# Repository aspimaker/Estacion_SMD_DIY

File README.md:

# Estacion_SMD_DIY
Base de soldadura SMD. Actualmente en desarrollo. No lo construyas todavía.

Utilizando un Arduino Nano, incluye el hardware necesario para calentar y controlar la temperatura usando una NTC y un SSR.
Incluye una pantalla OLED de 0.96", un enconder para moverse por el menú, algunos led y pulsadores.

Está diseñada para utilizar una tira led RGB los estados: frio, calentando, temperatura alcanzada, enfriando...
Puede que lo cambie por una tira WS2812B para simpliicar el diseño y la construcción.

Se podrán crear curvas de temperatura..

Agradezco tu colaboración para ayudarme a con posibles mejoras, corrección de errores, etc...

Gracias y un saludo.

#DIY_SMD_Station
SMD soldering station. Currently under development. Do not build it yet.

Using an Arduino Nano, it includes the necessary hardware for heating and temperature control using an NTC thermistor and an SSR.
It includes a 0.96" OLED screen, an encoder for navigating the menu, some LEDs, and pushbuttons.

It is designed to use an RGB LED strip with the following states: cold, heating, temperature reached, cooling, etc. I may change it to a WS2812B strip to simplify the design and construction.

Temperature curves can be created.

I appreciate your collaboration in helping me with possible improvements, bug fixes, etc.

Thank you and best regards.

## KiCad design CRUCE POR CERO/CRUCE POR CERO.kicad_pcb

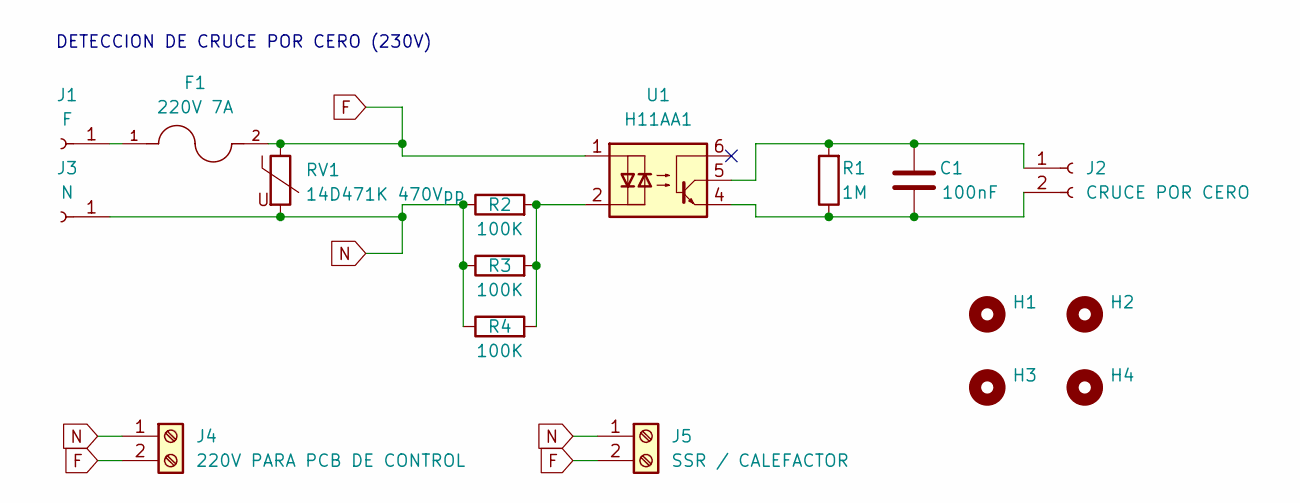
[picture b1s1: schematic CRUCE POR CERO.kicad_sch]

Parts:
C1: 100nF; C_Disc_D3.0mm_W2.0mm_P2.50mm
F1: 220V 7A; FUSIBLE BLX-A; PARTREV B
H1, H2, H3, H4: MountingHole; MountingHole_3.2mm_M3
J1: F; PinSocket_1x01_P2.54mm_Vertical
J2: CRUCE POR CERO; PinHeader_1x02_P2.54mm_Vertical
J3: N; PinSocket_1x01_P2.54mm_Vertical
J4: 220V PARA PCB DE CONTROL; TerminalBlock_Phoenix_MPT-0,5-2-2.54_1x02_P2.54mm_Horizontal
J5: SSR / CALEFACTOR; TerminalBlock_Phoenix_MPT-0,5-2-2.54_1x02_P2.54mm_Horizontal
R1: 1M; R_Axial_DIN0204_L3.6mm_D1.6mm_P5.08mm_Horizontal
R2, R3, R4: 100K; R_Axial_DIN0411_L9.9mm_D3.6mm_P5.08mm_Vertical
RV1: 14D471K 470Vpp; RV_Disc_D15.5mm_W7.5mm_P7.5mm
U1: H11AA1; DIP-6_W7.62mm

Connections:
F: F1.2, J4.2, J5.2, RV1.1, U1.1
N: J3.1, J4.1, J5.1, R2.1, R3.1, R4.1, RV1.2
unnamed: F1.1, J1.1
unnamed: C1.1, J2.1, R1.2, U1.5
unnamed: C1.2, J2.2, R1.1, U1.4
unnamed: R2.2, R3.2, R4.2, U1.2

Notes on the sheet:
DETECCION DE CRUCE POR CERO (230V)

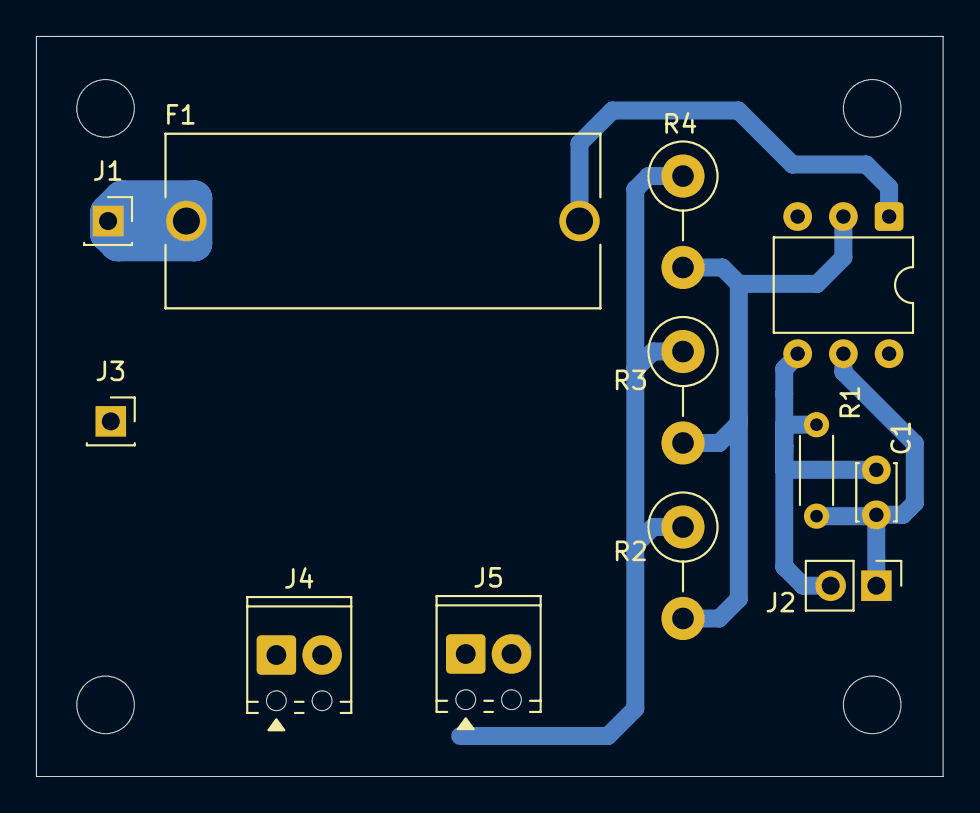
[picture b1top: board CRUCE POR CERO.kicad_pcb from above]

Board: 2 copper layers, 50.4 x 41.1 mm, 16 parts (0 on the bottom side), 6 nets.

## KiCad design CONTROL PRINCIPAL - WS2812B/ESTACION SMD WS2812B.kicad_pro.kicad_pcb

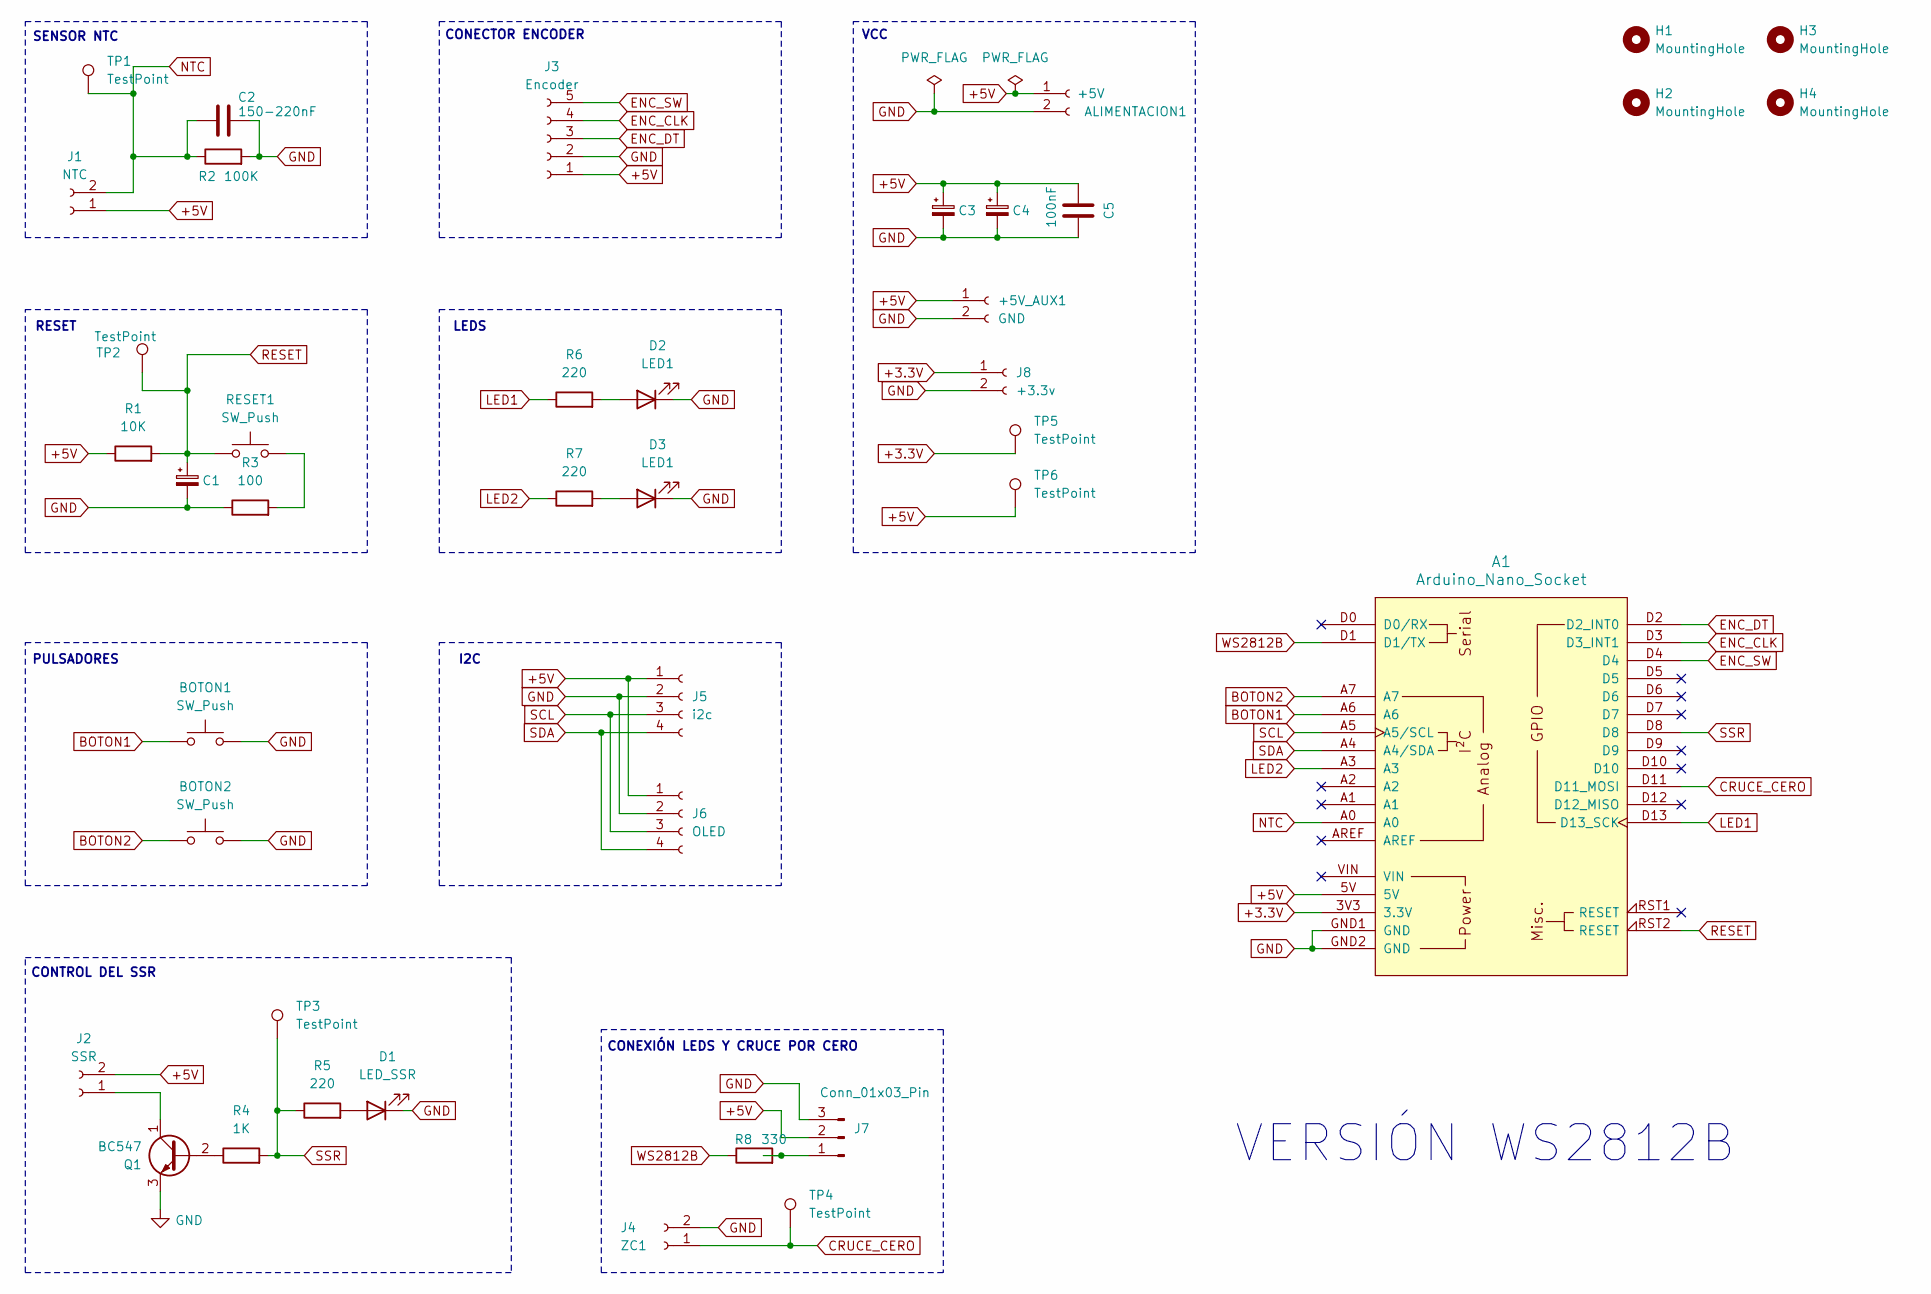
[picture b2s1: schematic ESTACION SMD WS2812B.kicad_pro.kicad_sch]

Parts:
+5V_AUX1: GND; PinHeader_1x02_P2.54mm_Vertical
A1: Arduino_Nano_Socket
ALIMENTACION1: +5V; PinHeader_1x02_P2.54mm_Vertical
BOTON1, BOTON2: SW_Push; PinHeader_1x02_P2.54mm_Vertical
C1, C4: 10uF/16V; CP_Radial_D5.0mm_P2.50mm
C2: 150-220nF; C_Disc_D3.0mm_W2.0mm_P2.50mm
C3: 1000uF/16V; CP_Radial_D10.0mm_P5.00mm
C5: 100nF; C_Disc_D3.0mm_W2.0mm_P2.50mm
D1: LED_SSR; LED_D3.0mm
D2, D3: LED1; LED_D3.0mm
H1, H2, H3, H4: MountingHole; MountingHole_3.2mm_M3
J1: NTC; PinHeader_1x02_P2.54mm_Vertical
J2: SSR; PinHeader_1x02_P2.54mm_Vertical
J3: Encoder; PinHeader_1x05_P2.54mm_Vertical
J4: ZC1; PinHeader_1x02_P2.54mm_Vertical
J5: i2c; PinHeader_1x04_P2.54mm_Vertical
J6: OLED; PinHeader_1x04_P2.54mm_Vertical
J7: Conn_01x03_Pin; PinHeader_1x03_P2.54mm_Vertical
J8: +3.3v; PinHeader_1x02_P2.54mm_Vertical
Q1: BC547; TO-92_Inline
R1: 10K; R_Axial_DIN0204_L3.6mm_D1.6mm_P5.08mm_Horizontal
R2: 100K; R_Axial_DIN0204_L3.6mm_D1.6mm_P5.08mm_Horizontal
R3: 100; R_Axial_DIN0204_L3.6mm_D1.6mm_P5.08mm_Horizontal
R4: 1K; R_Axial_DIN0204_L3.6mm_D1.6mm_P5.08mm_Horizontal
R5, R6, R7: 220; R_Axial_DIN0204_L3.6mm_D1.6mm_P5.08mm_Horizontal
R8: 330; R_Axial_DIN0204_L3.6mm_D1.6mm_P5.08mm_Horizontal
RESET1: SW_Push; PinHeader_1x02_P2.54mm_Vertical
TP1, TP2, TP3, TP4, TP5, TP6: TestPoint; TestPoint_Pad_1.5x1.5mm

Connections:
+3.3V: A1.3V3 (3.3V), J8.1, TP5.1
+5V: +5V_AUX1.1, A1.5V, ALIMENTACION1.1, C3.1, C4.1, C5.1, J1.1, J2.2, J3.1, J5.1, J6.1, J7.2, R1.1, TP6.1
BOTON1: A1.A6, BOTON1.1
BOTON2: A1.A7, BOTON2.1
CRUCE_CERO: A1.D11 (D11_MOSI), J4.1, TP4.1
ENC_CLK: A1.D3 (D3_INT1), J3.4
ENC_DT: A1.D2 (D2_INT0), J3.3
ENC_SW: A1.D4, J3.5
GND: +5V_AUX1.2, A1.GND1 (GND), A1.GND2 (GND), ALIMENTACION1.2, BOTON1.2, BOTON2.2, C1.2, C2.2, C3.2, C4.2, C5.2, D1.1 (K), D2.1 (K), D3.1 (K), J3.2, J4.2, J5.2, J6.2, J7.3, J8.2, Q1.3 (E), R2.2, R3.1
LED1: A1.D13 (D13_SCK), R6.1
LED2: A1.A3, R7.1
NTC: A1.A0, C2.1, J1.2, R2.1, TP1.1
unnamed: D1.2 (A), R5.2
unnamed: D2.2 (A), R6.2
unnamed: D3.2 (A), R7.2
unnamed: J2.1, Q1.1 (C)
unnamed: J7.1, R8.2
unnamed: Q1.2 (B), R4.1
unnamed: R3.2, RESET1.2
RESET: A1.RST2 (RESET), C1.1, R1.2, RESET1.1, TP2.1
SCL: A1.A5 (A5/SCL), J5.3, J6.3
SDA: A1.A4 (A4/SDA), J5.4, J6.4
SSR: A1.D8, R4.2, R5.1, TP3.1
WS2812B: A1.D1 (D1/TX), R8.1

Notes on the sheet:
CONTROL DEL SSR
I2C
CONECTOR ENCODER
PULSADORES
RESET
SENSOR NTC
CONEXIÓN LEDS Y CRUCE POR CERO
VERSIÓN WS2812B
VCC
LEDS

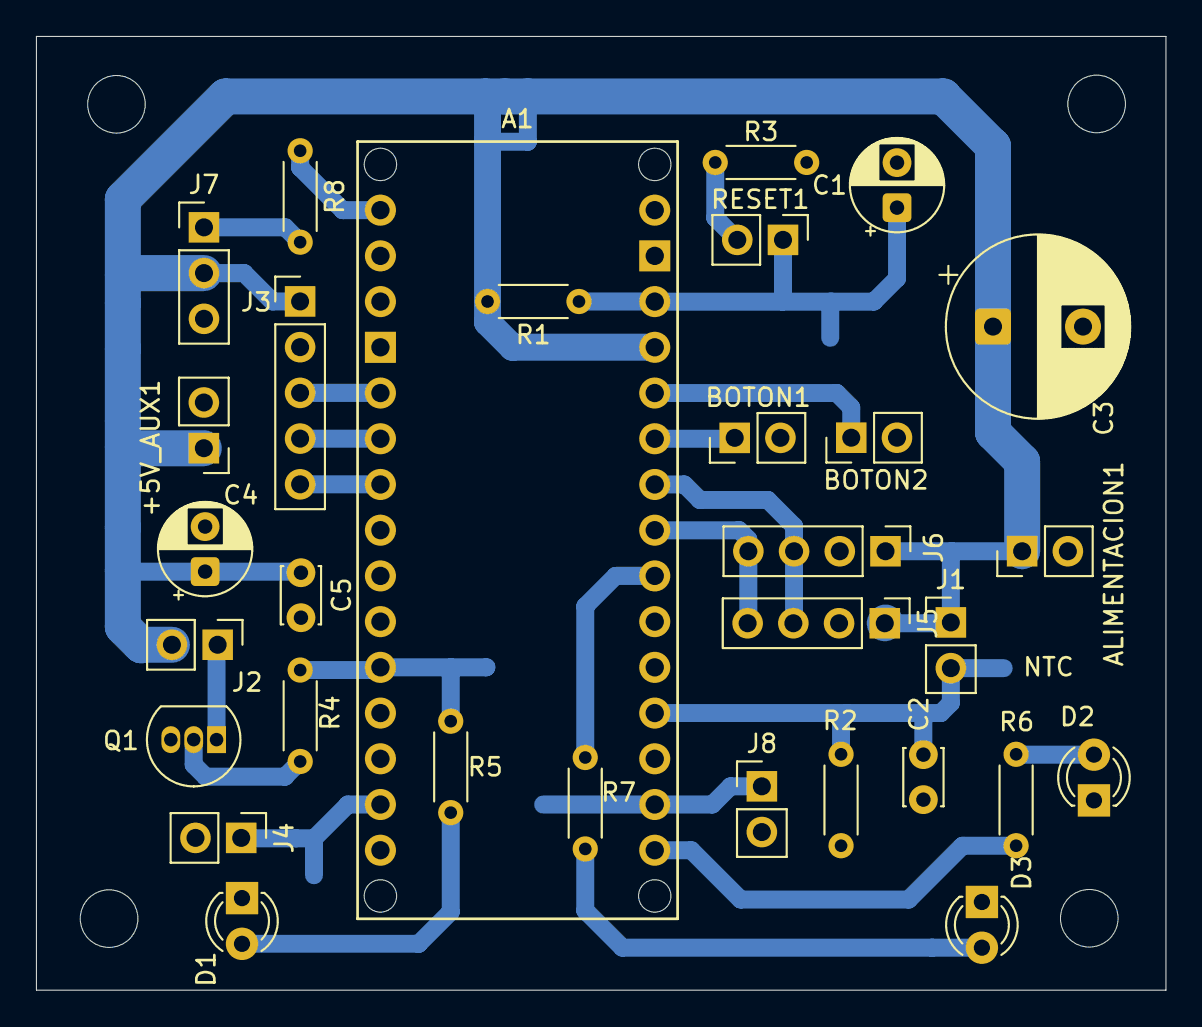
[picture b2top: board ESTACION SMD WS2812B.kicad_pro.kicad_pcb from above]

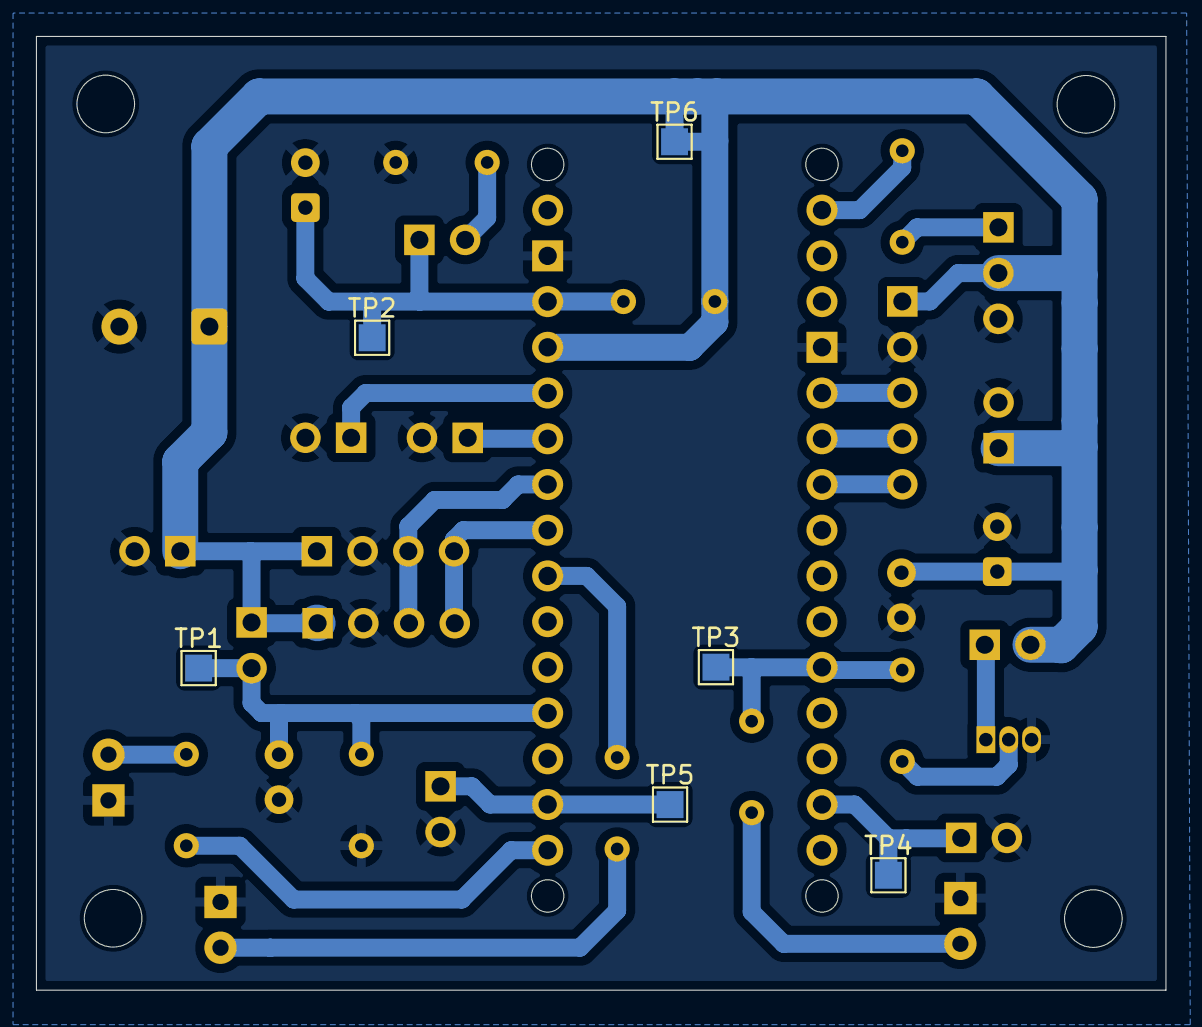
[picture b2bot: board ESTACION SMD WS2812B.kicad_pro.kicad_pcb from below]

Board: 2 copper layers, 62.8 x 53.0 mm, 41 parts (6 on the bottom side), 24 nets.

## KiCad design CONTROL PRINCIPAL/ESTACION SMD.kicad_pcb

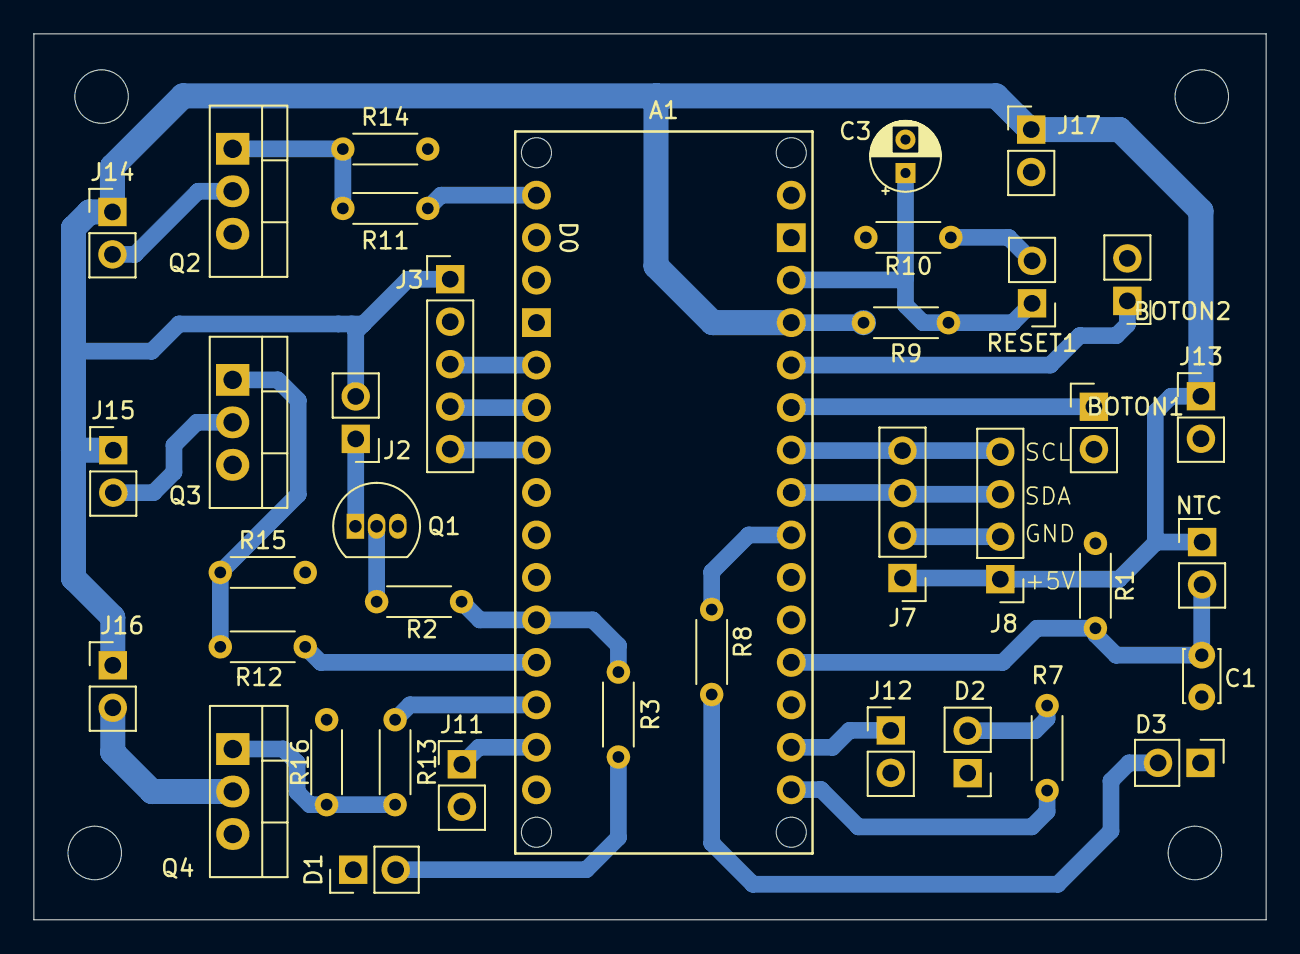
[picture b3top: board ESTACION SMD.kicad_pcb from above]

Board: 2 copper layers, 73.7 x 53.0 mm, 42 parts (0 on the bottom side), 31 nets.

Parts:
A1: Arduino_Nano_Socket
BOTON1, BOTON2: SW_Push; PinHeader_1x02_P2.54mm_Vertical
C1: 150-220nF; C_Disc_D3.0mm_W2.0mm_P2.50mm
C3: 16uF/16V; CP_Radial_D4.0mm_P2.00mm
D1: LED_SSR; PinHeader_1x02_P2.54mm_Vertical
D2, D3: LED1; PinHeader_1x02_P2.54mm_Vertical
H5, H6, H7, H8: MountingHole; MountingHole_3.2mm_M3
J1: NTC; PinHeader_1x02_P2.54mm_Vertical
J2: SSR; PinHeader_1x02_P2.54mm_Vertical
J3: Encoder; PinHeader_1x05_P2.54mm_Vertical
J7: i2c; PinHeader_1x04_P2.54mm_Vertical
J8: OLED; PinHeader_1x04_P2.54mm_Vertical
J11: ZC1; PinHeader_1x02_P2.54mm_Vertical
J12, J13: +3.3v; PinHeader_1x02_P2.54mm_Vertical
J14: LED_R; PinHeader_1x02_P2.54mm_Vertical
J15: LED_V; PinHeader_1x02_P2.54mm_Vertical
J16: LED_A; PinHeader_1x02_P2.54mm_Vertical
J17: VCC; PinHeader_1x02_P2.54mm_Vertical
Q1: BC547; TO-92_Inline
Q2, Q3, Q4: IRLZ44N; TO-220-3_Vertical
R1: 100K; R_Axial_DIN0204_L3.6mm_D1.6mm_P5.08mm_Horizontal
R2, R9: 1K; R_Axial_DIN0204_L3.6mm_D1.6mm_P5.08mm_Horizontal
R3, R7, R8, R11, R12, R13: 220; R_Axial_DIN0204_L3.6mm_D1.6mm_P5.08mm_Horizontal
R10: 100; R_Axial_DIN0204_L3.6mm_D1.6mm_P5.08mm_Horizontal
R14, R15, R16: 10K; R_Axial_DIN0204_L3.6mm_D1.6mm_P5.08mm_Horizontal
RESET1: SW_Push; PinHeader_1x02_P2.54mm_Vertical

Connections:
+3.3V: A1.3V3 (3.3V), J12.1
+5V: A1.5V, J1.1, J2.2, J3.1, J7.1, J8.1, J13.1, J14.1, J15.1, J16.1, J17.1, R9.1
Azul: A1.D10, R13.1
BOTON1: A1.A6, BOTON1.1
BOTON2: A1.A7, BOTON2.1
CRUCE_CERO: A1.D11 (D11_MOSI), J11.1
ENC_CLK: A1.D3 (D3_INT1), J3.4
ENC_DT: A1.D2 (D2_INT0), J3.3
ENC_SW: A1.D4, J3.5
GND: A1.GND1 (GND), A1.GND2 (GND), BOTON1.2, BOTON2.2, C1.2, C3.2, D1.1 (K), D2.1 (K), D3.1 (K), J3.2, J7.2, J8.2, J11.2, J12.2, J13.2, J17.2, Q1.3 (E), Q2.3 (S), Q3.3 (S), Q4.3 (S), R1.2, R10.1, R14.2, R15.2, R16.2
LED1: A1.D13 (D13_SCK), R7.1
LED2: A1.A3, R8.1
NTC: A1.A0, C1.1, J1.2, R1.1
unnamed: D1.2 (A), R3.2
unnamed: D2.2 (A), R7.2
unnamed: D3.2 (A), R8.2
unnamed: J2.1, Q1.1 (C)
unnamed: J14.2, Q2.2 (D)
unnamed: J15.2, Q3.2 (D)
unnamed: J16.2, Q4.2 (D)
unnamed: Q1.2 (B), R2.1
unnamed: Q2.1 (G), R11.2, R14.1
unnamed: Q3.1 (G), R12.2, R15.1
unnamed: Q4.1 (G), R13.2, R16.1
unnamed: R10.2, RESET1.2
RESET: A1.RST2 (RESET), C3.1, R9.2, RESET1.1
Rojo: A1.D1 (D1/TX), R11.1
SCL: A1.A5 (A5/SCL), J7.4, J8.4
SDA: A1.A4 (A4/SDA), J7.3, J8.3
SSR: A1.D8, R2.2, R3.1
Verde: A1.D9, R12.1

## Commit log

2025-07-26 README.md
2025-07-26 Código para Arduino Nano
2025-07-26 Esquema y PCB principal, en Kidad
2025-07-26 Esquema y PCB de la detección de paso por cero
2025-07-26 Imágenes
2025-12-09 Enhance README with project details and acknowledgments
    Updated README to include additional information in both Spanish and English about the SMD soldering station project, its current development status, and hardware details.
2025-12-09 actualización
